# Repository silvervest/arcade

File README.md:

# Arcade machine

This is a collection of circuits that I designed and built in order to build my own arcade machine.

I probably could have picked up off-the-shelf items for any and all of these, but I wanted to make my own for fun.

## Stick

Takes the joystick and buttons inputs and emulates two gamepads over USB. Each gamepad supports 16 buttons, which allows for four directionals and 12 actions per "player". The two players are provided by I2C I/O expanders.

The spare GPIO on the Pi Pico are expanded out as well, in case I'd like to use them later for something else.

## PSX

One of the goals of my machine was to support lightgun games, and I decided I wanted to use the existing Namco Guncon lightguns I already had. So this does that.

It also provides an additional 16 GPIO, for whatever else might take my fancy. With this and the spare GPIO above in the Stick, I could theoretically make a 4 player cabinet!

## VGA to RGB

Driving my arcade cabinet is a regular PC running Batocera, and I am using VGA output. The CRT I'm using can be modded to support RGB, and this board handles that stuff, plus converting the h+v sync signals from VGA into csync for the TV to handle.

The TV I used also has a quirk where it disables RGB blanking via "software" at startup, so this board's Pi Pico can interface with the i2c bus onboard the TV and send the commands to re-enable RGB blanking when ready, and I also made the Pico control RGB blanking, so we can make sure we don't enable blanking before the computer is booted to make sure we don't send a 30khz signal and damage anything...

## License

All PCB designs are [CERN OHL v2 Strongly Reciprocal licensed](LICENSE-HW.md)

All Software is [MIT licensed](LICENSE-SW.md)

Copyright 2024 silvestron's bits and bytes

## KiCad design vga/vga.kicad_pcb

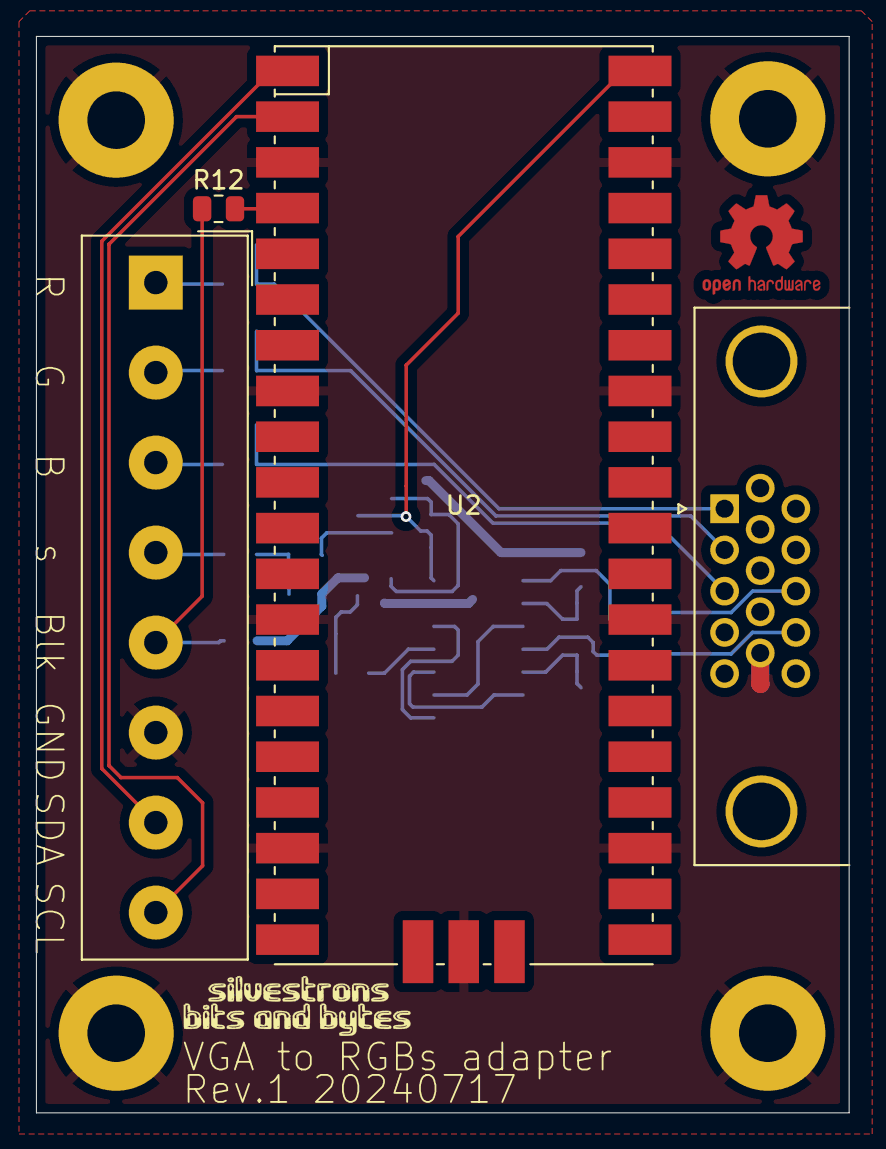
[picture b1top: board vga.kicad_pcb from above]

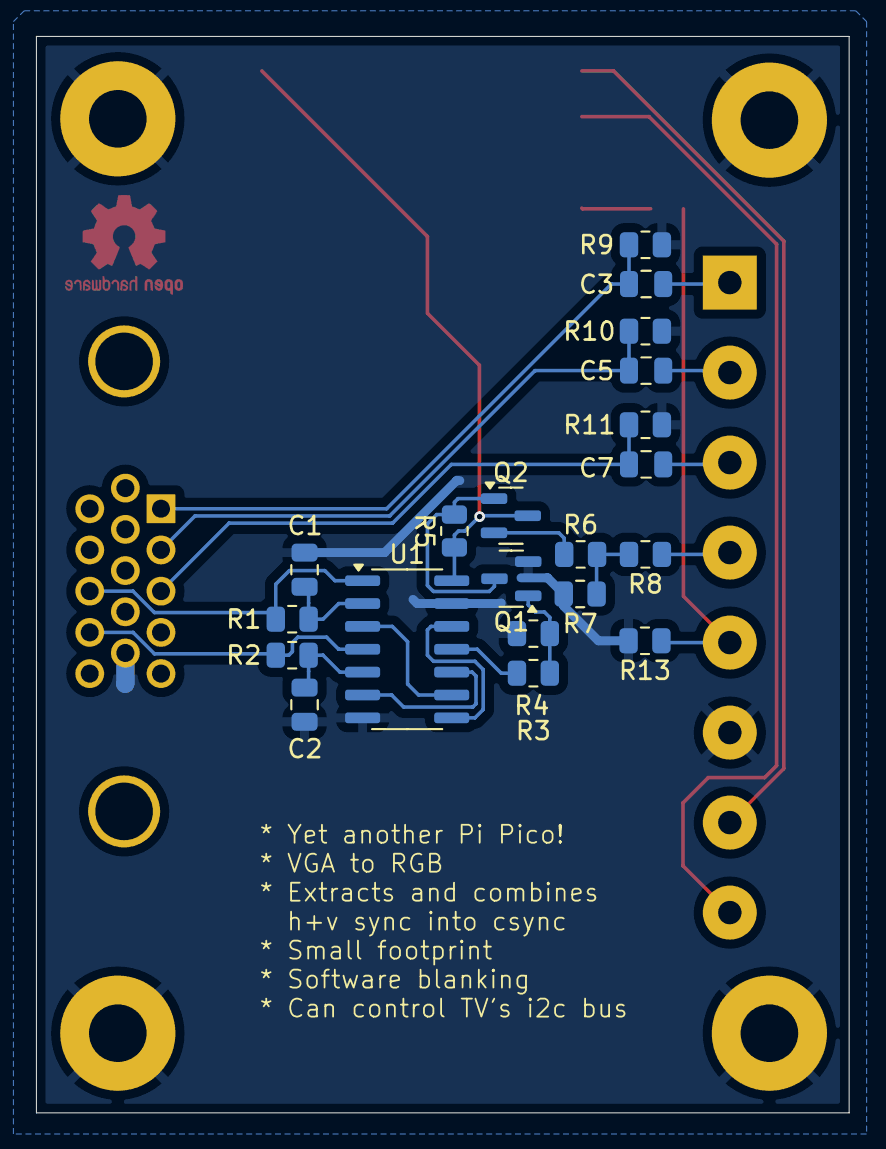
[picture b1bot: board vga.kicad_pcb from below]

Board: 2 copper layers, 45.2 x 59.8 mm, 28 parts (20 on the bottom side), 25 nets.

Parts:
C1, C2: 22uF; C_0805_2012Metric
C3, C5, C7: 100n; C_0805_2012Metric
H1, H1#2, H2, H2#2: MountingHole_Pad; MountingHole_3.2mm_M3_Pad
J1: VGA; DSUB-15-HD_Female_Horizontal_P2.29x1.98mm_EdgePinOffset3.03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
J2: TV Interface; Altech_AK100_1x08_P5.00mm
Q1, Q2: BC847; SOT-23
R1, R2: 2k2; R_0805_2012Metric
R3, R4: 1k8; R_0805_2012Metric
R5: 2k7; R_0805_2012Metric
R6, R7, R8: 47; R_0805_2012Metric
R9, R10, R11: 75; R_0805_2012Metric
R12: 1k0; R_0805_2012Metric
R13: 3k3; R_0805_2012Metric
U1: SN74LS86ADR; SOIC-14_3.9x8.7mm_P1.27mm
U2: Pico; RPi_Pico_SMD

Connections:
+5V: Q2.3 (C), R5.1, U1.14 (VCC), U2.40 (VBUS)
/AV1-1: J2.4, R8.1
/BIN2: C7.2, J2.3
/FBLIN2: J2.5, R12.2, R13.1
/GIN2: C5.2, J2.2
/IN B: C7.1, J1.3, R11.1
/IN BLK: R12.1, U2.4 (GPIO2)
/IN G: C5.1, J1.2, R10.1
/IN R: C3.1, J1.1, R9.1
/OUT R: C3.2, J2.1
/SCL: J2.8, U2.2 (GPIO1)
/SDA: J2.7, U2.1 (GPIO0)
GND: C1.2, C2.2, H1.1, H1#2.1, H2.1, H2#2.1, J1.10, J2.6, Q1.2 (E), R4.2, R7.2, R9.2, R10.2, R11.2, R13.2, U1.7 (GND), U1.13, U2.3 (GND), U2.8 (GND), U2.13 (GND), U2.18 (GND), U2.23 (GND), U2.28 (GND), U2.33 (AGND), U2.38 (GND), U2.42 (GND)
unnamed: C1.1, R1.2, U1.2
unnamed: C2.1, R2.2, U1.5
unnamed: J1.13, R1.1, U1.1
unnamed: J1.14, R2.1, U1.4
unnamed: Q1.1 (B), R3.2, R4.1
unnamed: Q1.3 (C), Q2.1 (B), R5.2
unnamed: Q2.2 (E), R6.1
unnamed: R3.1, U1.11
unnamed: R6.2, R7.1, R8.2
unnamed: U1.3, U1.9
unnamed: U1.6, U1.10
unnamed: U1.8, U1.12

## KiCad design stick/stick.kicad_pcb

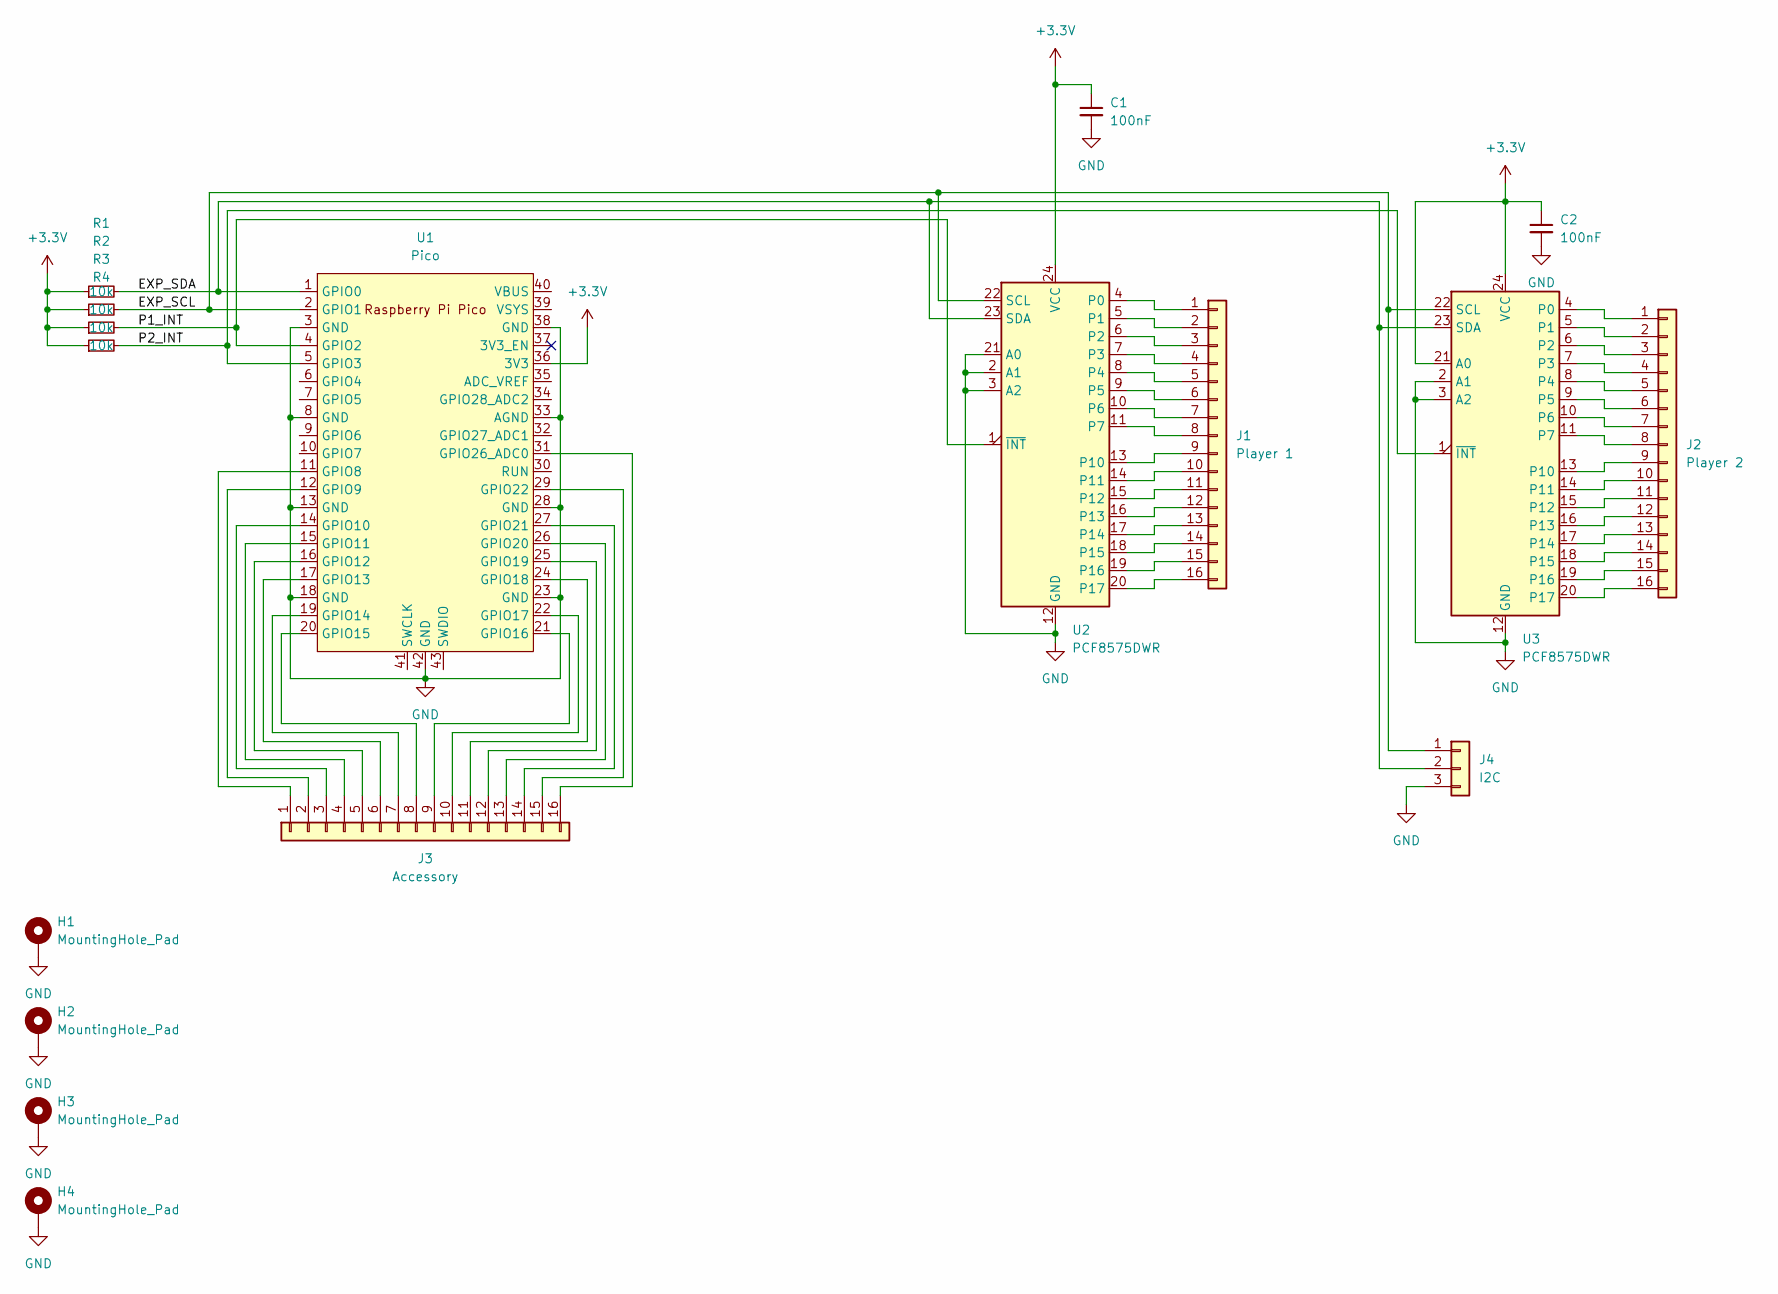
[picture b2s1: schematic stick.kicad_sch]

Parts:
C1, C2: 100nF; C_0805_2012Metric
H1, H2, H3, H4: MountingHole_Pad; MountingHole_3mm_Pad
J1: Player 1; Altech_AK100_1x16_P5.00mm
J2: Player 2; Altech_AK100_1x16_P5.00mm
J3: Accessory; Altech_AK100_1x16_P5.00mm
J4: I2C; Altech_AK100_1x03_P5.00mm
R1, R2, R3, R4: 10k; R_0805_2012Metric
U1: Pico; RPi_Pico_SMD_TH
U2, U3: PCF8575DWR; SOIC-24W_7.5x15.4mm_P1.27mm; LCSC C2863388

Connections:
+3.3V: C1.1, C2.1, R1.1, R2.1, R3.1, R4.1, U1.36 (3V3), U2.24 (VCC), U3.21 (A0), U3.24 (VCC)
/EXP_SCL: J4.1, R2.2, U1.2 (GPIO1), U2.22 (SCL), U3.22 (SCL)
/EXP_SDA: J4.2, R1.2, U1.1 (GPIO0), U2.23 (SDA), U3.23 (SDA)
/P1_INT: R3.2, U1.4 (GPIO2), U2.1 (~INT)
/P2_INT: R4.2, U1.5 (GPIO3), U3.1 (~INT)
GND: C1.2, C2.2, H1.1, H2.1, H3.1, H4.1, J4.3, U1.3 (GND), U1.8 (GND), U1.13 (GND), U1.18 (GND), U1.23 (GND), U1.28 (GND), U1.33 (AGND), U1.38 (GND), U1.42 (GND), U2.2 (A1), U2.3 (A2), U2.12 (GND), U2.21 (A0), U3.2 (A1), U3.3 (A2), U3.12 (GND)
unnamed: J1.1, U2.4 (P0)
unnamed: J1.2, U2.5 (P1)
unnamed: J1.3, U2.6 (P2)
unnamed: J1.4, U2.7 (P3)
unnamed: J1.5, U2.8 (P4)
unnamed: J1.6, U2.9 (P5)
unnamed: J1.7, U2.10 (P6)
unnamed: J1.8, U2.11 (P7)
unnamed: J1.9, U2.13 (P10)
unnamed: J1.10, U2.14 (P11)
unnamed: J1.11, U2.15 (P12)
unnamed: J1.12, U2.16 (P13)
unnamed: J1.13, U2.17 (P14)
unnamed: J1.14, U2.18 (P15)
unnamed: J1.15, U2.19 (P16)
unnamed: J1.16, U2.20 (P17)
unnamed: J2.1, U3.4 (P0)
unnamed: J2.2, U3.5 (P1)
unnamed: J2.3, U3.6 (P2)
unnamed: J2.4, U3.7 (P3)
unnamed: J2.5, U3.8 (P4)
unnamed: J2.6, U3.9 (P5)
unnamed: J2.7, U3.10 (P6)
unnamed: J2.8, U3.11 (P7)
unnamed: J2.9, U3.13 (P10)
unnamed: J2.10, U3.14 (P11)
unnamed: J2.11, U3.15 (P12)
unnamed: J2.12, U3.16 (P13)
unnamed: J2.13, U3.17 (P14)
unnamed: J2.14, U3.18 (P15)
unnamed: J2.15, U3.19 (P16)
unnamed: J2.16, U3.20 (P17)
unnamed: J3.1, U1.11 (GPIO8)
unnamed: J3.2, U1.12 (GPIO9)
unnamed: J3.3, U1.14 (GPIO10)
unnamed: J3.4, U1.15 (GPIO11)
unnamed: J3.5, U1.16 (GPIO12)
unnamed: J3.6, U1.17 (GPIO13)
unnamed: J3.7, U1.19 (GPIO14)
unnamed: J3.8, U1.20 (GPIO15)
unnamed: J3.9, U1.21 (GPIO16)
unnamed: J3.10, U1.22 (GPIO17)
unnamed: J3.11, U1.24 (GPIO18)
unnamed: J3.12, U1.25 (GPIO19)
unnamed: J3.13, U1.26 (GPIO20)
unnamed: J3.14, U1.27 (GPIO21)
unnamed: J3.15, U1.29 (GPIO22)
unnamed: J3.16, U1.31 (GPIO26_ADC0)

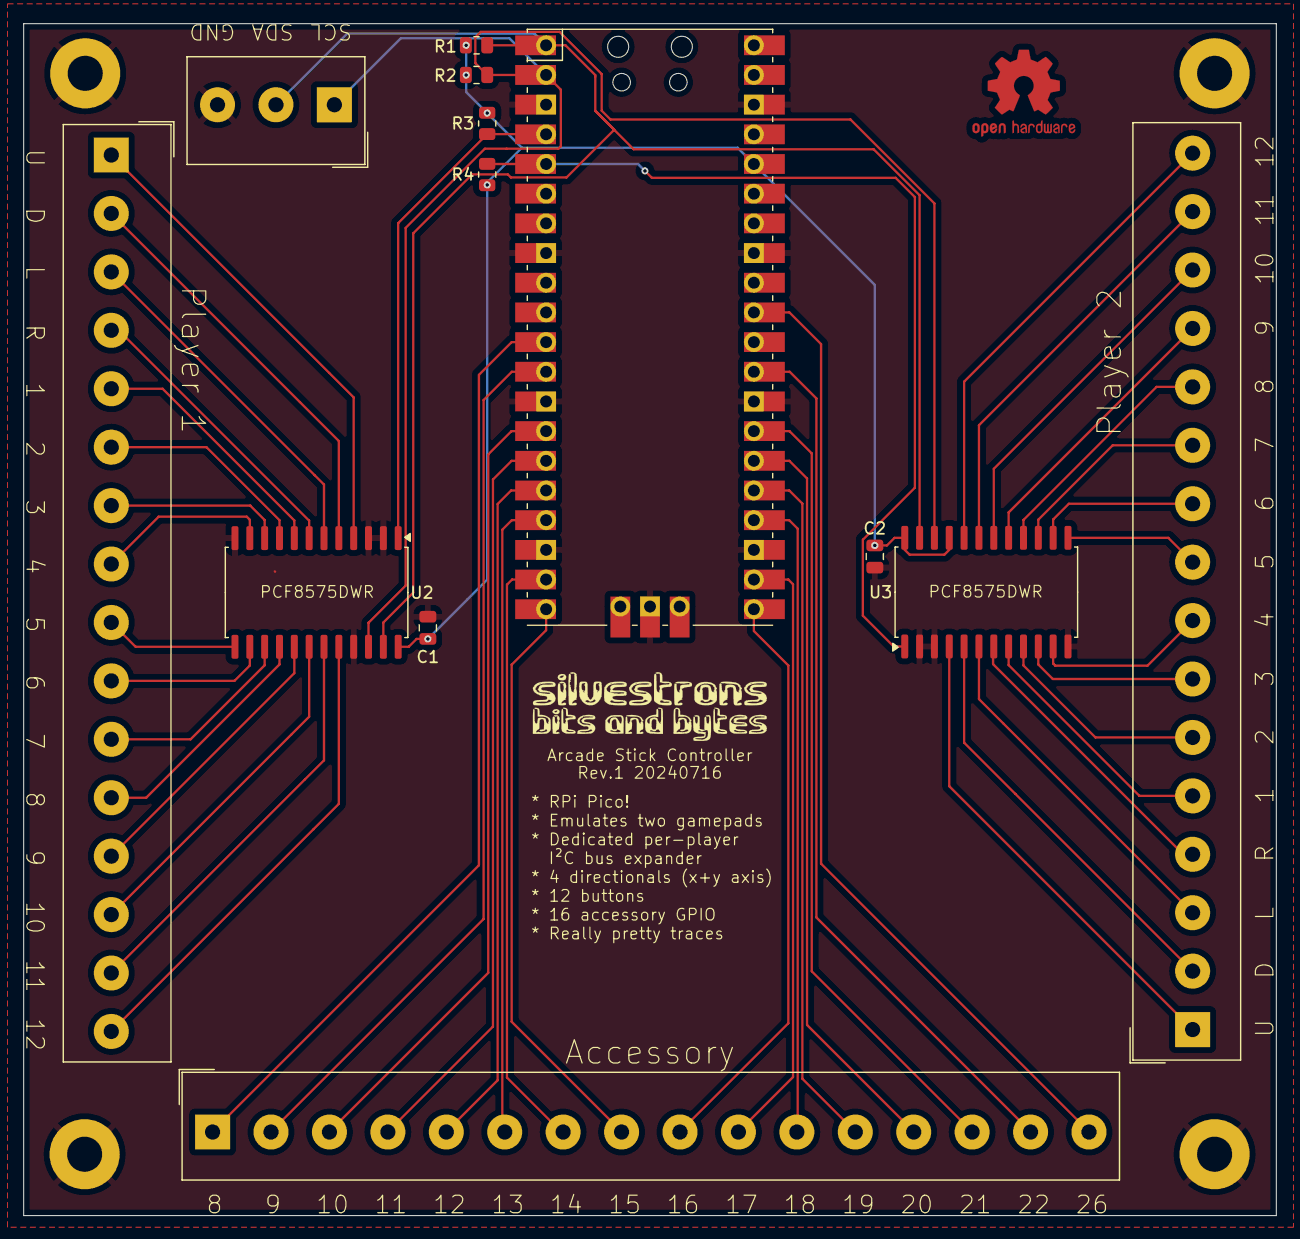
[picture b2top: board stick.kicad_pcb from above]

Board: 2 copper layers, 107.2 x 102.0 mm, 17 parts (0 on the bottom side), 54 nets.

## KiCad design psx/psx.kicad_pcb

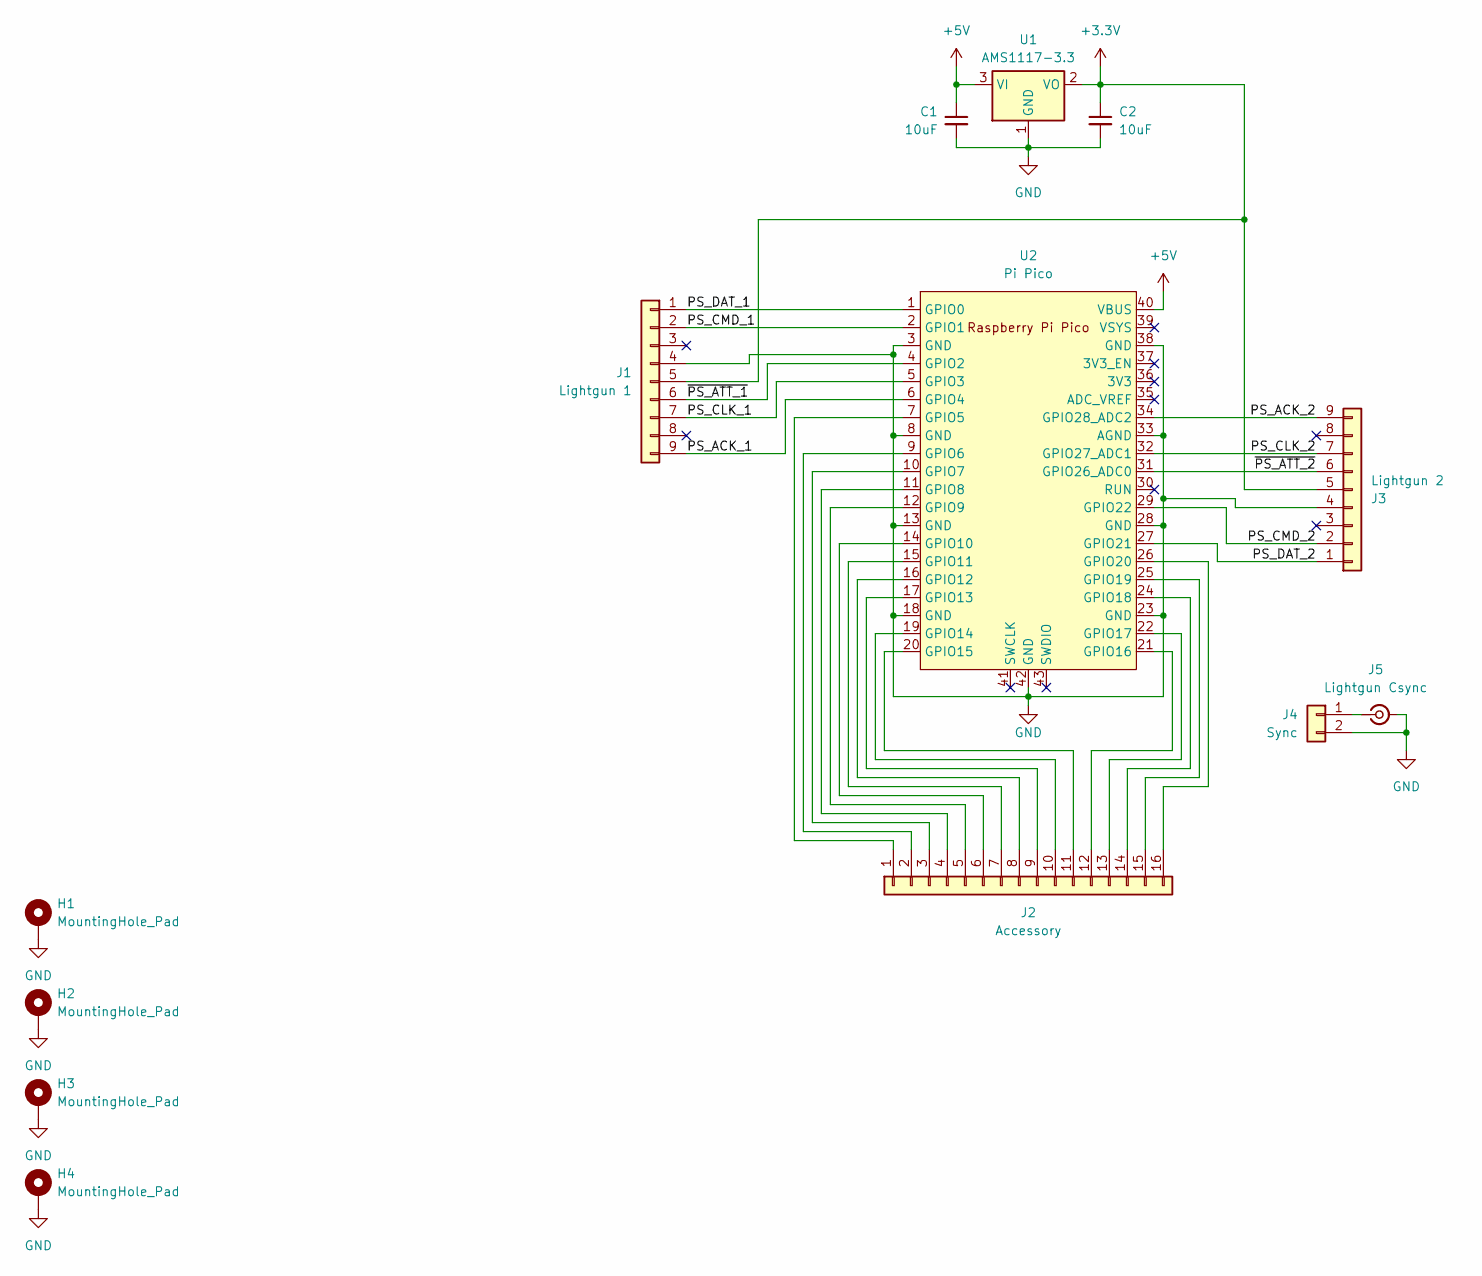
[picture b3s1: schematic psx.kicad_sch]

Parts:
C1, C2: 10uF; C_0805_2012Metric
H1, H2, H3, H4: MountingHole_Pad; MountingHole_3mm_Pad
J1: Lightgun 1; PSX_Pad_Connector
J2: Accessory; Altech_AK100_1x16_P5.00mm
J3: Lightgun 2; PSX_Pad_Connector
J4: Sync; Altech_AK100_1x02_P5.00mm
J5: Lightgun Csync; CUI_RCJ-047
U1: AMS1117-3.3; SOT-223-3_TabPin2
U2: Pi Pico; RPi_Pico_SMD_TH

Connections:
+3.3V: C2.1, J1.5, J3.5, U1.2 (VO)
+5V: C1.1, U1.3 (VI), U2.40 (VBUS)
/PS_ACK_1: J1.9, U2.6 (GPIO4)
/PS_ACK_2: J3.9, U2.34 (GPIO28_ADC2)
/PS_CLK_1: J1.7, U2.5 (GPIO3)
/PS_CLK_2: J3.7, U2.32 (GPIO27_ADC1)
/PS_CMD_1: J1.2, U2.2 (GPIO1)
/PS_CMD_2: J3.2, U2.29 (GPIO22)
/PS_DAT_1: J1.1, U2.1 (GPIO0)
/PS_DAT_2: J3.1, U2.27 (GPIO21)
/~PS_ATT_1: J1.6, U2.4 (GPIO2)
/~PS_ATT_2: J3.6, U2.31 (GPIO26_ADC0)
GND: C1.2, C2.2, H1.1, H2.1, H3.1, H4.1, J1.4, J3.4, J4.2, J5.2 (Ext), U1.1 (GND), U2.3 (GND), U2.8 (GND), U2.13 (GND), U2.18 (GND), U2.23 (GND), U2.28 (GND), U2.33 (AGND), U2.38 (GND), U2.42 (GND)
unnamed: J2.1, U2.7 (GPIO5)
unnamed: J2.2, U2.9 (GPIO6)
unnamed: J2.3, U2.10 (GPIO7)
unnamed: J2.4, U2.11 (GPIO8)
unnamed: J2.5, U2.12 (GPIO9)
unnamed: J2.6, U2.14 (GPIO10)
unnamed: J2.7, U2.15 (GPIO11)
unnamed: J2.8, U2.16 (GPIO12)
unnamed: J2.9, U2.17 (GPIO13)
unnamed: J2.10, U2.19 (GPIO14)
unnamed: J2.11, U2.20 (GPIO15)
unnamed: J2.12, U2.21 (GPIO16)
unnamed: J2.13, U2.22 (GPIO17)
unnamed: J2.14, U2.24 (GPIO18)
unnamed: J2.15, U2.25 (GPIO19)
unnamed: J2.16, U2.26 (GPIO20)
unnamed: J4.1, J5.1 (In)

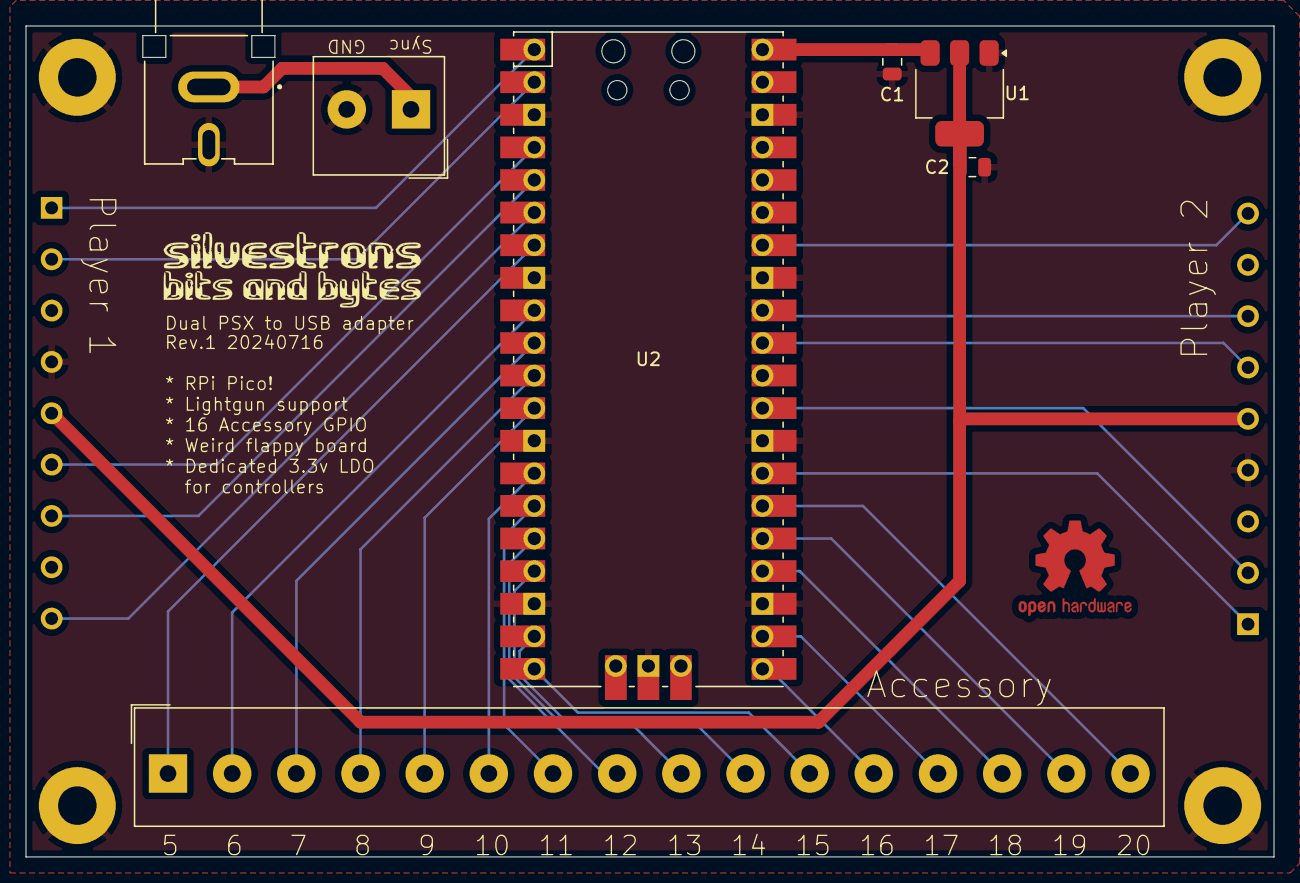
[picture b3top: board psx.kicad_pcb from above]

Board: 2 copper layers, 97.2 x 64.8 mm, 13 parts (0 on the bottom side), 30 nets.

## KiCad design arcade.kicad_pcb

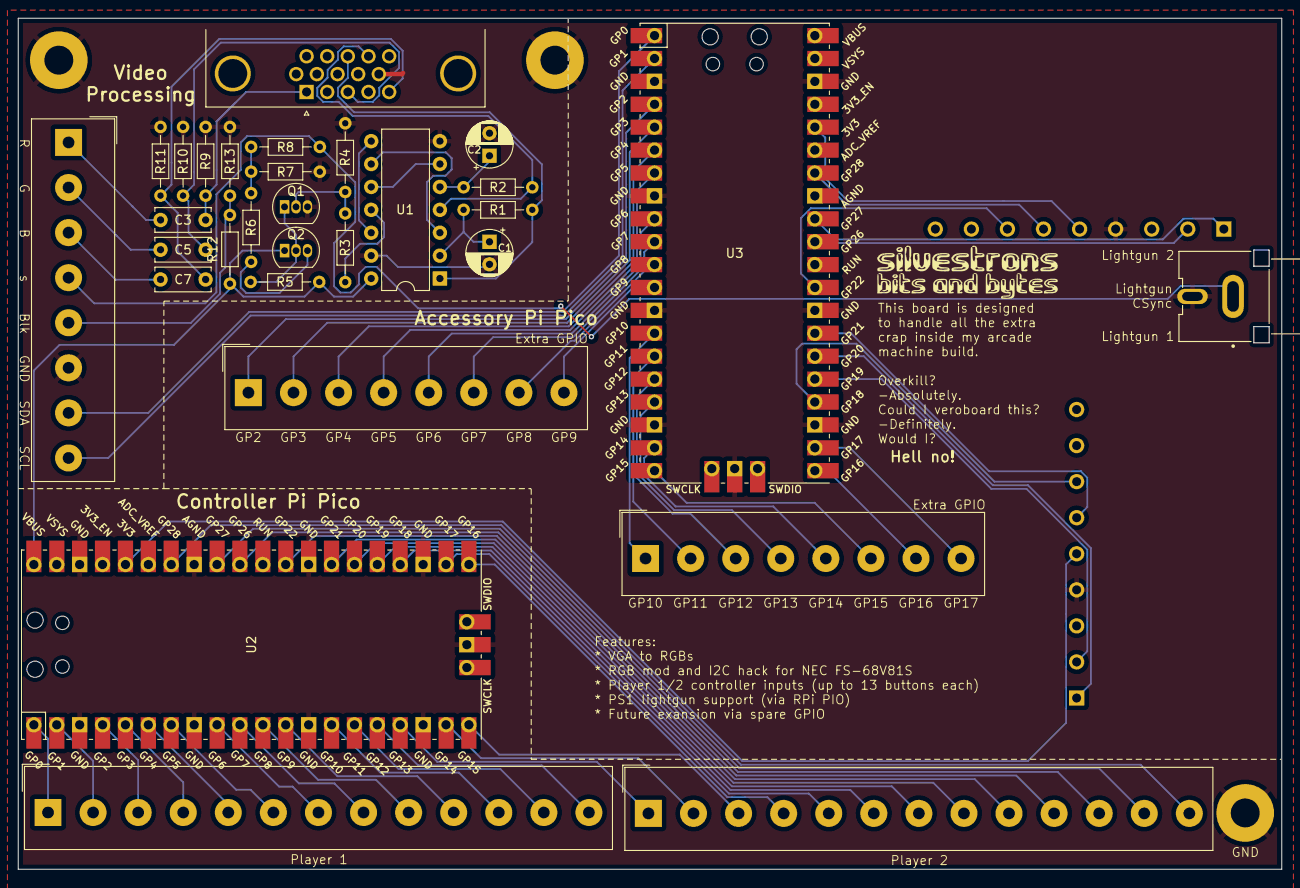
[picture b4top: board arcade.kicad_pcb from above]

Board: 2 copper layers, 140.1 x 94.4 mm, 35 parts (0 on the bottom side), 76 nets.

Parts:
C1, C2: 22uF; CP_Radial_D5.0mm_P2.50mm
C3, C5, C7: 100n; C_Disc_D6.0mm_W2.5mm_P5.00mm
H1, H2, H2#2: MountingHole_Pad; MountingHole_3.2mm_M3_Pad
J1: VGA; DSUB-15-HD_Female_Horizontal_P2.29x1.98mm_EdgePinOffset3.03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
J2: TV Interface; Altech_AK100_1x08_P5.00mm
J3: Player 1; Altech_AK100_1x13_P5.00mm
J4: Player 2; Altech_AK100_1x13_P5.00mm
J5, J6: Extra GPIO; Altech_AK100_1x08_P5.00mm
J7: Lightgun 1; PSX_Pad_Connector
J8: Lightgun 2; PSX_Pad_Connector
J9: Lightgun Csync; CUI_RCJ-047
Q1, Q2: BC547; TO-92_Inline
R1, R2: 2k2; R_Axial_DIN0204_L3.6mm_D1.6mm_P7.62mm_Horizontal
R3, R4: 1k8; R_Axial_DIN0204_L3.6mm_D1.6mm_P7.62mm_Horizontal
R5: 2k7; R_Axial_DIN0204_L3.6mm_D1.6mm_P7.62mm_Horizontal
R6, R7, R8: 47; R_Axial_DIN0204_L3.6mm_D1.6mm_P7.62mm_Horizontal
R9, R10, R11: 75; R_Axial_DIN0204_L3.6mm_D1.6mm_P7.62mm_Horizontal
R12, R13: 1k0; R_Axial_DIN0204_L3.6mm_D1.6mm_P7.62mm_Horizontal
U1: 74LS86; DIP-14_W7.62mm
U2: Controller Pico; RPi_Pico_SMD_TH
U3: Accessory Pico; RPi_Pico_SMD_TH

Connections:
+3.3V: J8.5, U3.36 (3V3)
+3.3VP: J7.5, U2.36 (3V3)
+5V: Q2.1 (C), R5.1, R12.1, U1.14 (VCC), U2.40 (VBUS), U3.40 (VBUS)
/IO/GPIO0: J3.1, U2.1 (GPIO0)
/IO/GPIO1: J3.2, U2.2 (GPIO1)
/IO/GPIO2: J3.3, U2.4 (GPIO2)
/IO/GPIO3: J3.4, U2.5 (GPIO3)
/IO/GPIO4: J3.5, U2.6 (GPIO4)
/IO/GPIO5: J3.6, U2.7 (GPIO5)
/IO/GPIO6: J3.7, U2.9 (GPIO6)
/IO/GPIO7: J3.8, U2.10 (GPIO7)
/IO/GPIO8: J3.9, U2.11 (GPIO8)
/IO/GPIO9: J3.10, U2.12 (GPIO9)
/IO/GPIO10: J3.11, U2.14 (GPIO10)
/IO/GPIO11: J3.12, U2.15 (GPIO11)
/IO/GPIO12: J3.13, U2.16 (GPIO12)
/IO/GPIO13: J4.1, U2.17 (GPIO13)
/IO/GPIO14: J4.2, U2.19 (GPIO14)
/IO/GPIO15: J4.3, U2.20 (GPIO15)
/IO/GPIO16: J4.4, U2.21 (GPIO16)
/IO/GPIO17: J4.5, U2.22 (GPIO17)
/IO/GPIO18: J4.6, U2.24 (GPIO18)
/IO/GPIO19: J4.7, U2.25 (GPIO19)
/IO/GPIO20: J4.8, U2.26 (GPIO20)
/IO/GPIO21: J4.9, U2.27 (GPIO21)
/IO/GPIO22: J4.10, U2.29 (GPIO22)
/IO/GPIO23: J4.11, U2.31 (GPIO26_ADC0)
/IO/GPIO24: J4.12, U2.32 (GPIO27_ADC1)
/IO/GPIO25: J4.13, U2.34 (GPIO28_ADC2)
/IO/GPIO26: J5.1, U3.4 (GPIO2)
/IO/GPIO27: J5.2, U3.5 (GPIO3)
/IO/GPIO28: J5.3, U3.6 (GPIO4)
/IO/GPIO29: J5.4, U3.7 (GPIO5)
/IO/GPIO30: J5.5, U3.9 (GPIO6)
/IO/GPIO31: J5.6, U3.10 (GPIO7)
/IO/GPIO32: J5.7, U3.11 (GPIO8)
/IO/GPIO33: J5.8, U3.12 (GPIO9)
/IO/GPIO34: J6.1, U3.14 (GPIO10)
/IO/GPIO35: J6.2, U3.15 (GPIO11)
/IO/GPIO36: J6.3, U3.16 (GPIO12)
/IO/GPIO37: J6.4, U3.17 (GPIO13)
/IO/GPIO38: J6.5, U3.19 (GPIO14)
/IO/GPIO39: J6.6, U3.20 (GPIO15)
/IO/GPIO40: J6.7, U3.21 (GPIO16)
/IO/GPIO41: J6.8, U3.22 (GPIO17)
/IO/PS_CLK_1: J7.7, U3.24 (GPIO18)
/IO/PS_CLK_2: J8.7, U3.29 (GPIO22)
/IO/PS_CMD_1: J7.2, U3.25 (GPIO19)
/IO/PS_CMD_2: J8.2, U3.31 (GPIO26_ADC0)
/IO/PS_DAT_1: J7.1, U3.26 (GPIO20)
/IO/PS_DAT_2: J8.1, U3.32 (GPIO27_ADC1)
/IO/SCL: J2.8, U3.2 (GPIO1)
/IO/SDA: J2.7, U3.1 (GPIO0)
/IO/~PS_ATT_1: J7.6, U3.27 (GPIO21)
/IO/~PS_ATT_2: J8.6, U3.34 (GPIO28_ADC2)
/Video Processing/AV1-1: J2.4, J9.1 (In), R8.1
/Video Processing/BIN2: C7.2, J2.3
/Video Processing/FBLIN2: J2.5, R12.2, R13.1
/Video Processing/GIN2: C5.2, J2.2
/Video Processing/IN B: C7.1, J1.5, R11.1
/Video Processing/IN G: C5.1, J1.3, R10.1
/Video Processing/IN R: C3.1, J1.1, R9.1
/Video Processing/RIN2: C3.2, J2.1
GND: C1.2, C2.2, H1.1, H2.1, H2#2.1, J1.10, J2.6, J7.4, J8.4, J9.2 (Ext), Q1.3 (E), R4.2, R7.2, R9.2, R10.2, R11.2, R13.2, U1.7 (GND), U1.13, U2.3 (GND), U2.8 (GND), U2.13 (GND), U2.18 (GND), U2.23 (GND), U2.28 (GND), U2.33 (AGND), U2.38 (GND), U2.42 (GND), U3.3 (GND), U3.8 (GND), U3.13 (GND), U3.18 (GND), U3.23 (GND), U3.28 (GND), U3.38 (GND), U3.42 (GND)
unnamed: C1.1, R1.2, U1.2
unnamed: C2.1, R2.2, U1.5
unnamed: J1.13, R1.1, U1.1
unnamed: J1.14, R2.1, U1.4
unnamed: Q1.2 (B), R3.2, R4.1
unnamed: Q1.1 (C), Q2.2 (B), R5.2
unnamed: Q2.3 (E), R6.1
unnamed: R3.1, U1.11
unnamed: R6.2, R7.1, R8.2
unnamed: U1.3, U1.9
unnamed: U1.6, U1.10
unnamed: U1.8, U1.12

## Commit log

2024-06-23 second design for nec tv and with inputs integrated
2024-07-05 code!
2024-07-17 big update of hardware modules
2024-08-01 fix incorrect footprint in vga board; rewrite stick codebase to use pcf8575 i/o expanders and vga codebase to fix bugs and support rgb blanking
